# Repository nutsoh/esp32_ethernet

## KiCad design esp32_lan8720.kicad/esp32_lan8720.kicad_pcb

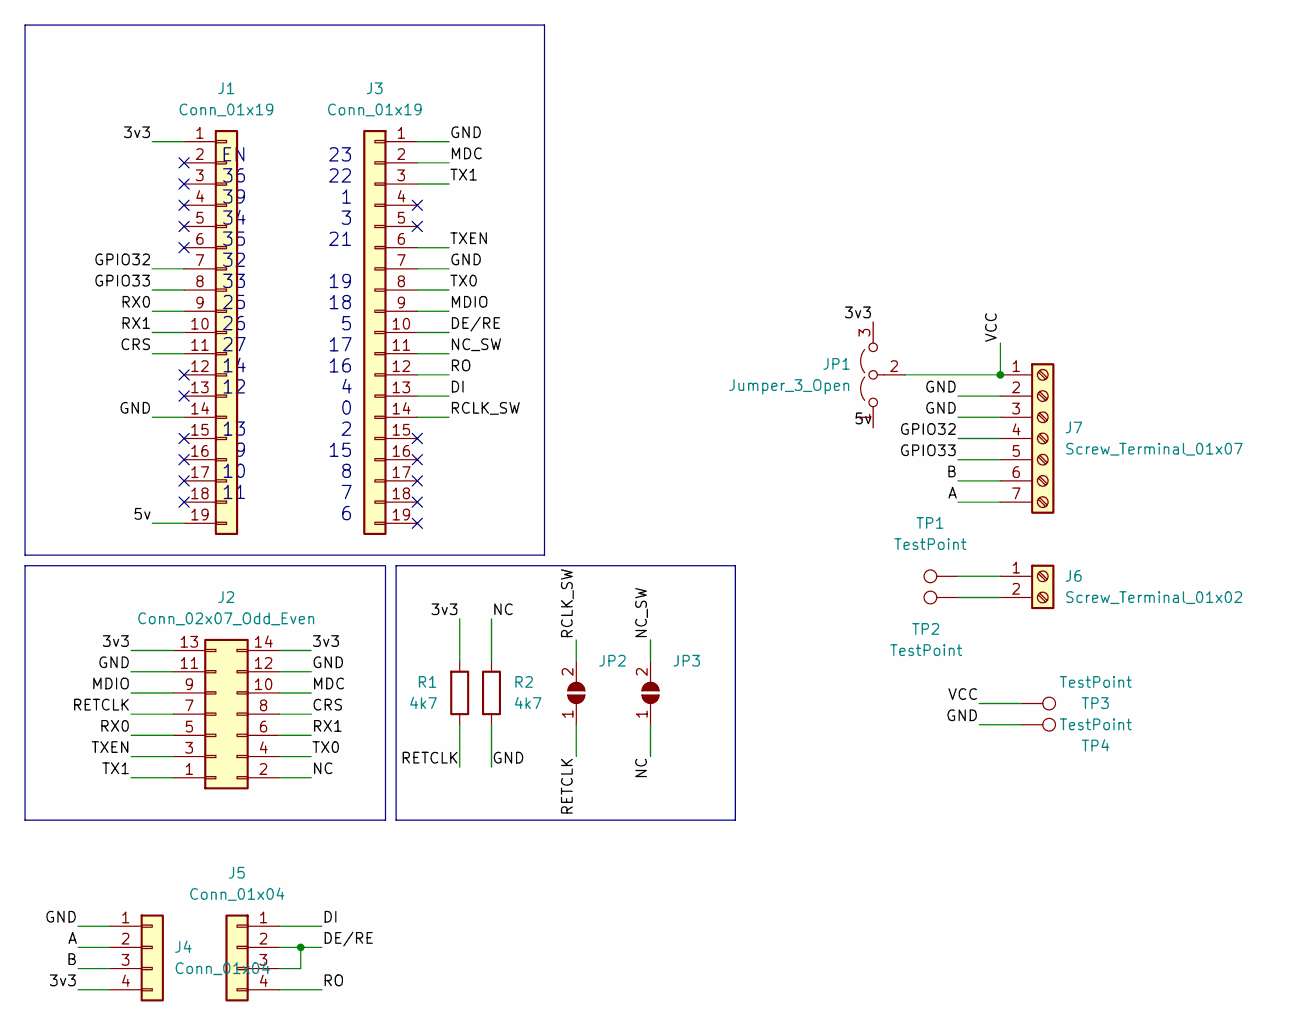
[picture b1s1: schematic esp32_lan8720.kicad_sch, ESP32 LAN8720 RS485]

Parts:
J1, J3: Conn_01x19; PinSocket_1x19_P2.54mm_Vertical
J2: Conn_02x07_Odd_Even; PinSocket_2x07_P2.54_Vertical_Hybrid_SMD_THT_DBLSIDED
J4, J5: Conn_01x04; PinSocket_1x04_P2.54mm_Vertical
J6: Screw_Terminal_01x02; TerminalBlock_MetzConnect_Type171_RT13702HBWC_1x02_P7.50mm_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
J7: Screw_Terminal_01x07; TerminalBlock_RND_205-00050_1x07_P5.00mm_Horizontal
JP1: Jumper_3_Open; PinHeader_1x03_P2.54mm_Vertical
JP2, JP3: SolderJumper_2_Open; SolderJumper-2_P1.3mm_Open_RoundedPad1.0x1.5mm
R1, R2: 4k7; R_1206_3216Metric
TP1, TP2: TestPoint; TestPoint_THTPad_D2.5mm_Drill1.2mm
TP3, TP4: TestPoint; TestPoint_THTPad_D2.0mm_Drill1.0mm

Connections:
/3v3: J1.1, J2.13, J2.14, J4.4, JP1.3 (B), R1.2
/5v: J1.19, JP1.1 (A)
/A: J4.2, J7.7
/B: J4.3, J7.6
/CRS: J1.11, J2.8
/DE/RE: J3.10, J5.2, J5.3
/DI: J3.13, J5.1
/GND: J1.14, J2.11, J2.12, J3.1, J3.7, J4.1, J7.2, J7.3, R2.2, TP4.1
/GPIO32: J1.7, J7.4
/GPIO33: J1.8, J7.5
/MDC: J2.10, J3.2
/MDIO: J2.9, J3.9
/NC: J2.2, JP3.1 (A), R2.1
/NC_SW: J3.11, JP3.2 (B)
/RCLK_SW: J3.14, JP2.2 (B)
/RETCLK: J2.7, JP2.1 (A), R1.1
/RO: J3.12, J5.4
/RX0: J1.9, J2.5
/RX1: J1.10, J2.6
/TX0: J2.4, J3.8
/TX1: J2.1, J3.3
/TXEN: J2.3, J3.6
/VCC: J7.1, JP1.2 (C), TP3.1
unnamed: J6.1, TP1.1
unnamed: J6.2, TP2.1

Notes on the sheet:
23 22 1 3 21 19 18 5 17 16 4 0 2 15 8 7 6
EN 36 39 34 35 32 33 25 26 27 14 12 13 9 10 11

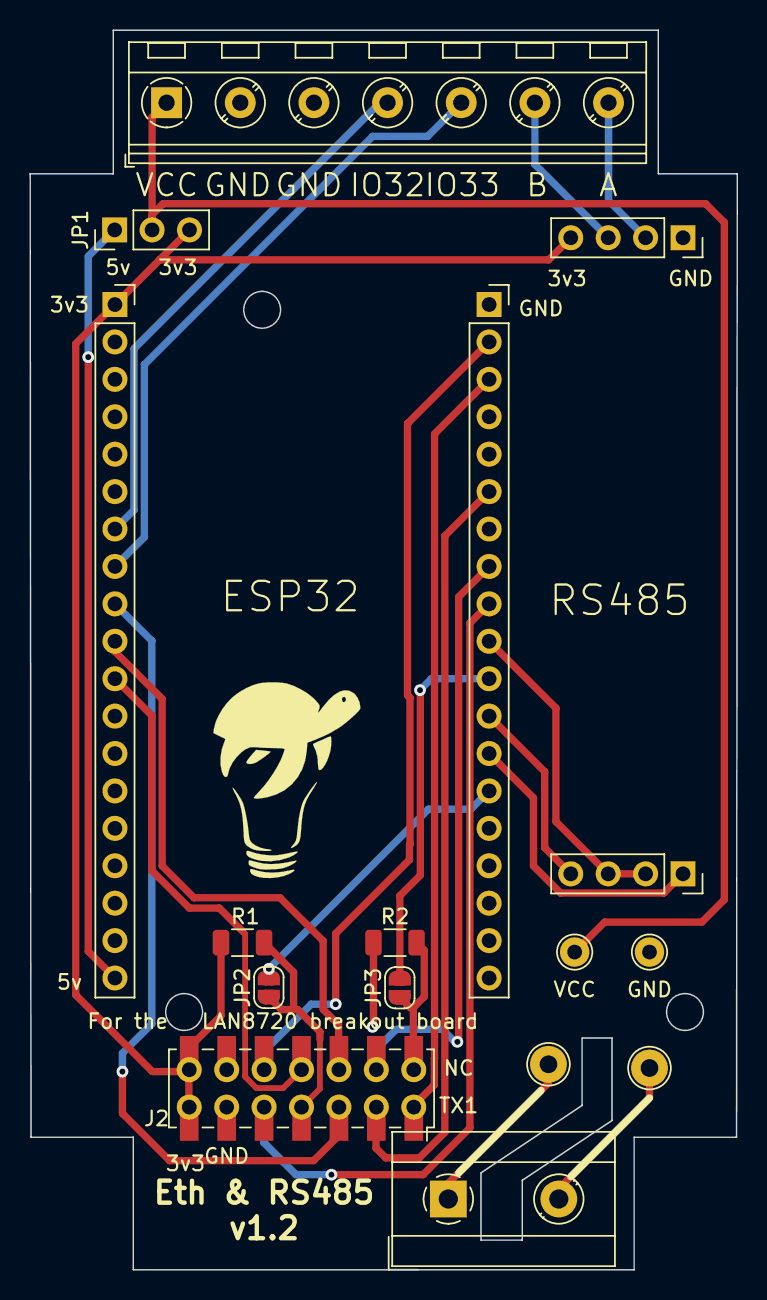
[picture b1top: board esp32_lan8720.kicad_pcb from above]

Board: 2 copper layers, 48.0 x 84.1 mm, 16 parts (0 on the bottom side), 25 nets.

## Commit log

2023-01-24 kicad files for v1.0 PCB
2023-01-24 kicad files for v1.1 PCB
2023-01-24 kicad files for v1.2 PCB
